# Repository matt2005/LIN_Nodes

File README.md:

Firmware and PCB designs for various LIN network nodes intended for retrofitting older vehicles.

```
boards/
    Eagle schematic and PCB files.

common/
    Protocol definitions and generator.

dashboard/
    Dashboard display using a 64x32 RGB LED panel driven by an NXP LPC1114.

Documentation/
    Datasheets for various parts used in the design.

lintool
    Host-side configuration tool. Talks to the usb_link hardware.

nodes/
    All of the nodes in this part of the tree are based on the Atmel ATTiny167.

    bl_core/
        LIN bootloader core, consumed by bl_installer.

    bl_installer/
        Bootloader installer; flashed onto a fresh board this will install the
        bootloader.

        The installed bootloader comes up on NAD 32 and can be flashed with lintool
        by explicitly supplying the node address and firmware file.

        lintool update -n 32 <path-to-fw-file>

        Only one node can be in this 'recovery' mode on the network when doing this.

    lib/
        Shared code.

    master/
        Network master node. Supports 7 switch-to-battery and 14 switch-to-ground
        inputs. 4 of the switch-to-ground inputs can also be 0-5V voltage inputs,
        with optional 2 or 16mA current sources for measuring resistive sensors.

    power_v3/
        5-output power switching node using Freescale smart high-side switches.
        Board limited to 5.5A, but code should work with the 10A device as well.
        Outputs support PWM, current monitoring, open- and short-circuit detection,
        overcurrent and overtemperature protection, etc.

    usb_link/
        USB bridge with support for configuration and node firmware updates.

```

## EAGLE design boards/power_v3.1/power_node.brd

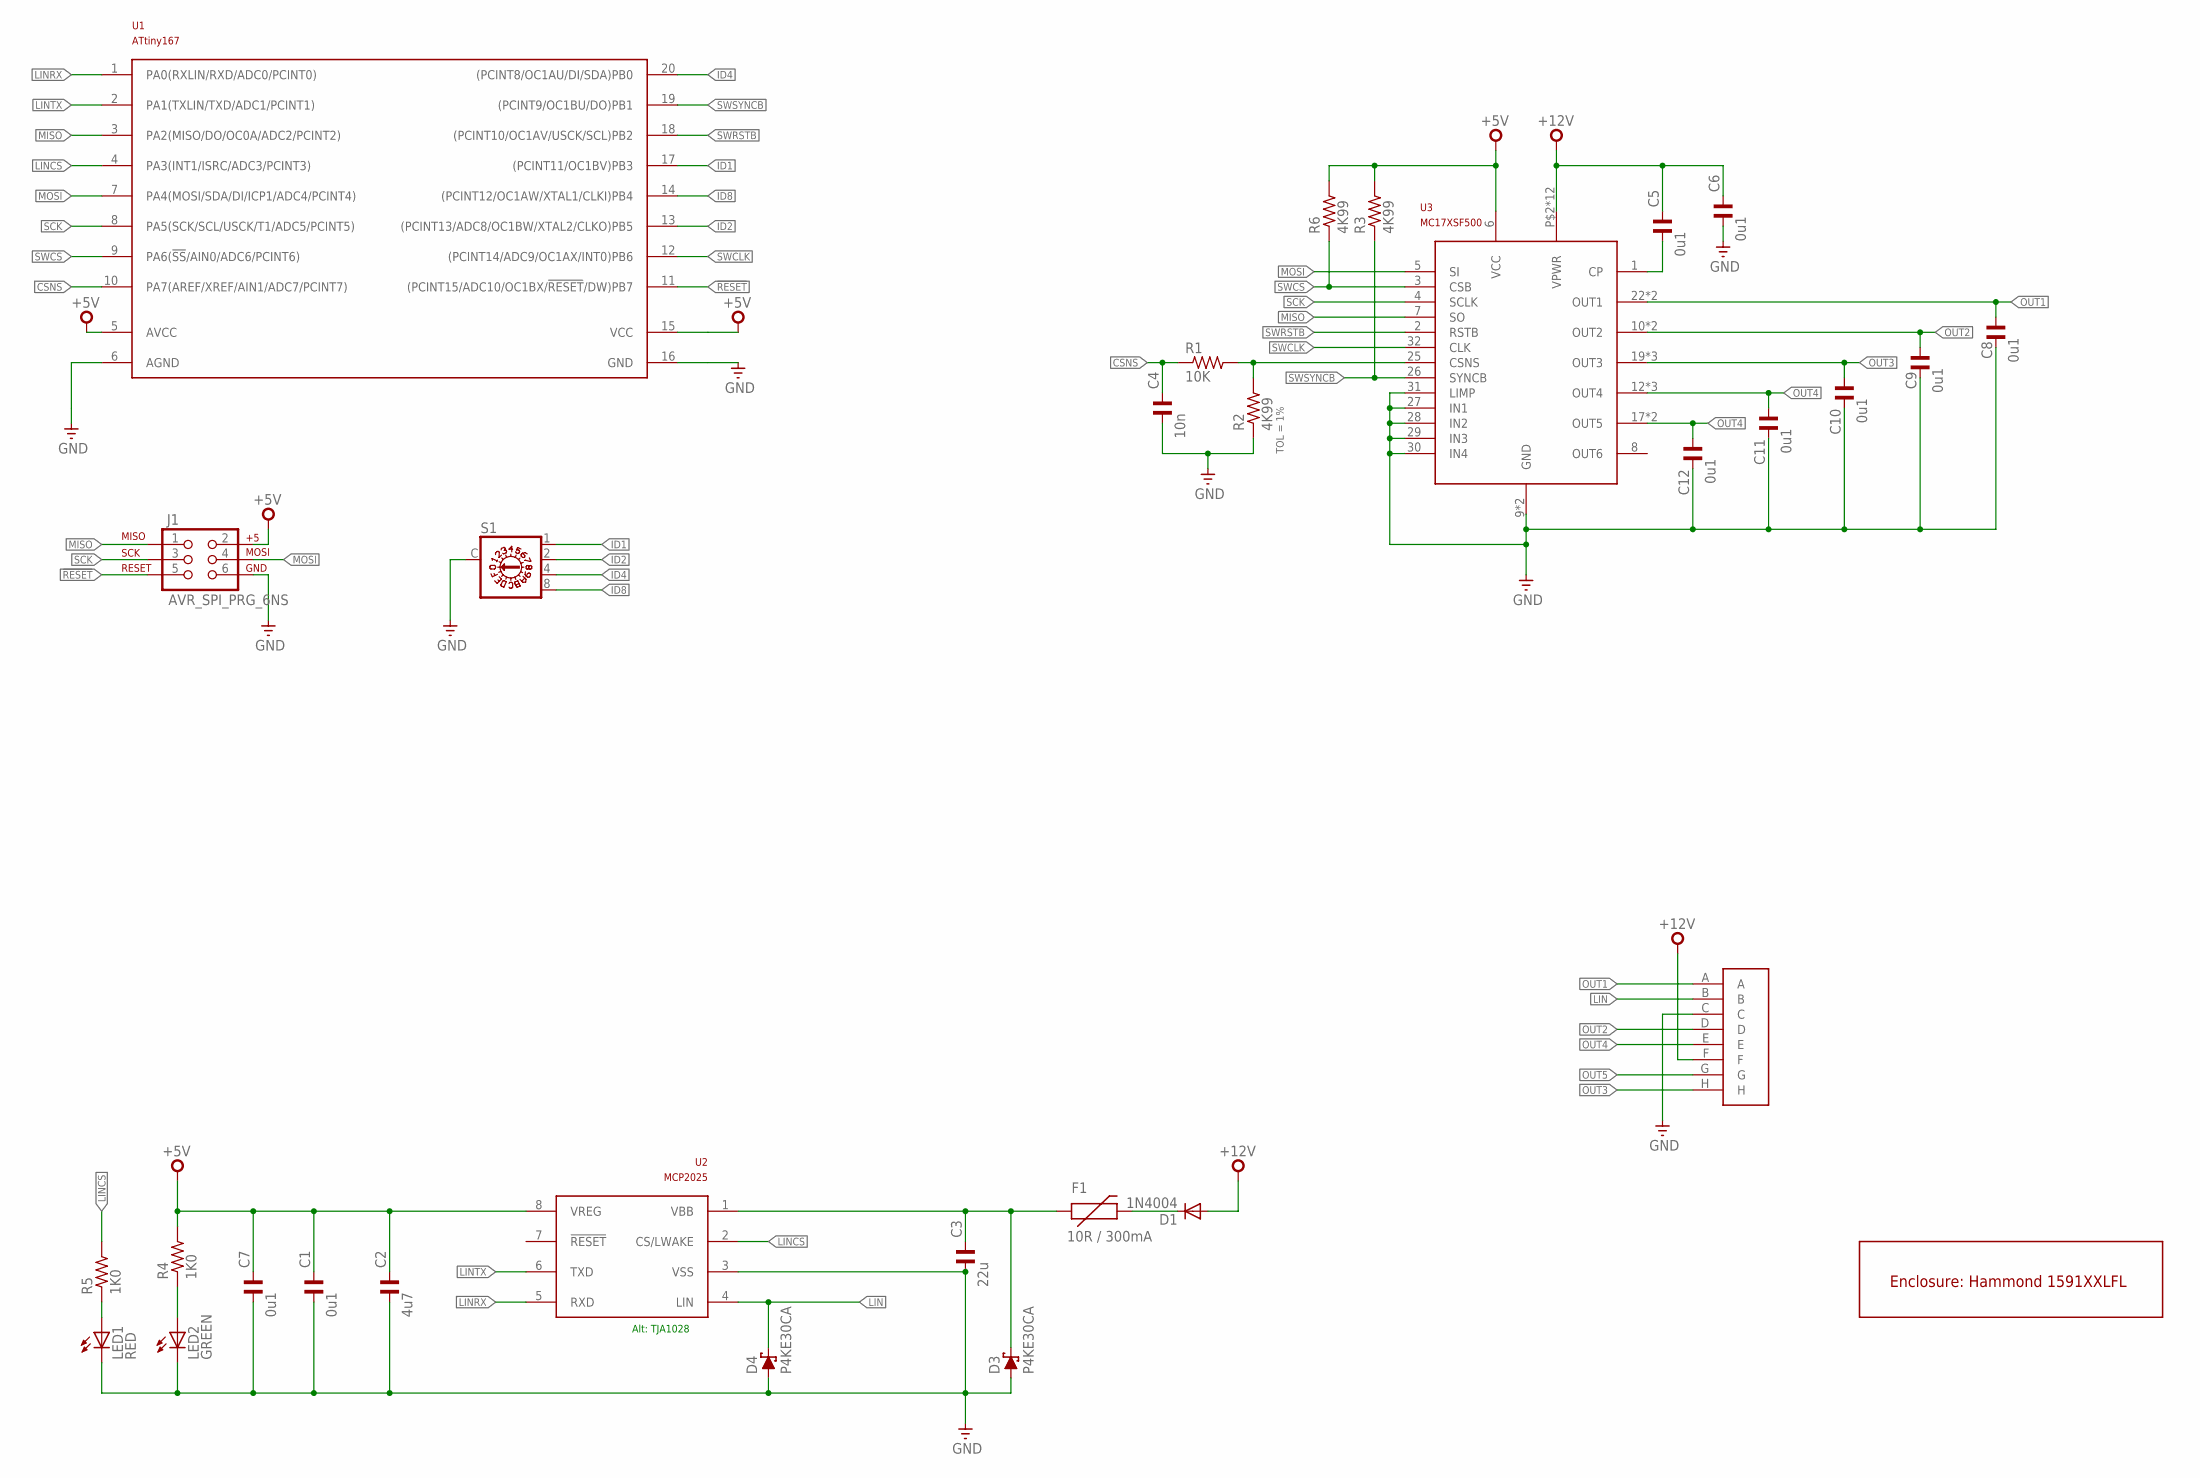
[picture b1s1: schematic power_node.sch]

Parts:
C1, C5, C6, C7: 0u1; C050-024X044; PARTNO FK28X7R1H104K
C2: 4u7; C050-024X044; PARTNO FK28X5R0J475K
C3: 22u; C050-024X044; PARTNO FK22X5R1E226M
C4: 10n; C025-024X044; PARTNO FK18X7R1H103K
C8, C9, C10, C11, C12: 0u1; C0603K; PARTNO C1608X7R1H104M080AA
D1: 1N4004; DO41-10; PARTNO 1N4004-TP
D3, D4: P4KE30CA; DO41-10; PARTNO P4KE30CA
F1: 10R / 300mA; PTC; PARTNO CMF-RL10-0
J1: AVR_SPI_PRG_6NS; 2X3-NS
J2: 12146734; PARTNO 12146724-B
LED1: RED; LED3MM; PARTNO C4SMF-RJS-CT0W0BB2
LED2: GREEN; LED3MM; PARTNO C4SMF-GJS-CV0Y0792
R1: 10K; 0207/10; PARTNO CF14JT10K0
R2, R3, R6: 4K99; 0207/10; PARTNO MFR-25FBF52-4K99
R4, R5: 1K0; 0207/10; PARTNO CF14JT1K00
S1: P103; PARTNO SH-7050MC
U1: ATtiny167; SO20W; PARTNO ATTINY167-SU
U2: MCP2025; SO08; PARTNO MCP2025-500E/SN
U3: MC17XSF500; SOIC32W-EP; PARTNO MC17XSF500EK
U$1: 1591XXLFL; PARTNO 1591XXLFLBK

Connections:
!RESET: J1.5, U1.11 ((PCINT15/ADC10/OC1BX/!RESET!/DW)PB7)
+5V: C1.1, C2.1, C7.1, J1.2, R3.2, R4.2, R6.2, U1.5 (AVCC), U1.15 (VCC), U2.8 (VREG), U3.6 (VCC)
+12V: C5.1, C6.1, D1.A, J2.F, U3.P$2 (VPWR), U3.P$3 (VPWR), U3.P$4 (VPWR), U3.P$5 (VPWR), U3.P$6 (VPWR), U3.P$7 (VPWR), U3.P$8 (VPWR), U3.P$9 (VPWR), U3.P$10 (VPWR), U3.P$11 (VPWR), U3.P$12 (VPWR), U3.P$13 (VPWR)
CSNS: C4.1, R1.1, U1.10 (PA7(AREF/XREF/AIN1/ADC7/PCINT7))
GND: C1.2, C2.2, C3.2, C4.2, C6.2, C7.2, C8.2, C9.2, C10.2, C11.2, C12.2, D3.A, D4.A, J1.6, J2.C, LED1.K (C), LED2.K (C), R2.1, S1.C, U1.6 (AGND), U1.16 (GND), U2.3 (VSS), U3.9 (GND), U3.24 (GND), U3.27 (IN1), U3.28 (IN2), U3.29 (IN3), U3.30 (IN4), U3.31 (LIMP)
ID1: S1.1, U1.17 ((PCINT11/OC1BV)PB3)
ID2: S1.2, U1.13 ((PCINT13/ADC8/OC1BW/XTAL2/CLKO)PB5)
ID4: S1.4, U1.20 ((PCINT8/OC1AU/DI/SDA)PB0)
ID8: S1.8, U1.14 ((PCINT12/OC1AW/XTAL1/CLKI)PB4)
LIN: D4.C, J2.B, U2.4 (LIN)
LINCS: R5.2, U1.4 (PA3(INT1/ISRC/ADC3/PCINT3)), U2.2 (CS/LWAKE)
LINRX: U1.1 (PA0(RXLIN/RXD/ADC0/PCINT0)), U2.5 (RXD)
LINTX: U1.2 (PA1(TXLIN/TXD/ADC1/PCINT1)), U2.6 (TXD)
MISO: J1.1, U1.3 (PA2(MISO/DO/OC0A/ADC2/PCINT2)), U3.7 (SO)
MOSI: J1.4, U1.7 (PA4(MOSI/SDA/DI/ICP1/ADC4/PCINT4)), U3.5 (SI)
unnamed: C5.2, U3.1 (CP)
unnamed: C3.1, D3.C, F1.P$1 (1), U2.1 (VBB)
unnamed: LED1.A, R5.1
unnamed: LED2.A, R4.1
unnamed: D1.C, F1.P$2 (2)
unnamed: R1.2, R2.2, U3.25 (CSNS)
OUT1: C8.1, J2.A, U3.22 (OUT1), U3.23 (OUT1)
OUT2: C9.1, J2.D, U3.10 (OUT2), U3.11 (OUT2)
OUT3: C10.1, J2.H, U3.19 (OUT3), U3.20 (OUT3), U3.21 (OUT3)
OUT4: C11.1, J2.E, U3.12 (OUT4), U3.13 (OUT4), U3.14 (OUT4)
OUT5: C12.1, J2.G, U3.17 (OUT5), U3.18 (OUT5)
SCK: J1.3, U1.8 (PA5(SCK/SCL/USCK/T1/ADC5/PCINT5)), U3.4 (SCLK)
SWCLK: U1.12 ((PCINT14/ADC9/OC1AX/INT0)PB6), U3.32 (CLK)
SWCS: R6.1, U1.9 (PA6(!SS!/AIN0/ADC6/PCINT6)), U3.3 (CSB)
SWRSTB: U1.18 ((PCINT10/OC1AV/USCK/SCL)PB2), U3.2 (RSTB)
SWSYNCB: R3.1, U1.19 ((PCINT9/OC1BU/DO)PB1), U3.26 (SYNCB)

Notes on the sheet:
Alt: TJA1028

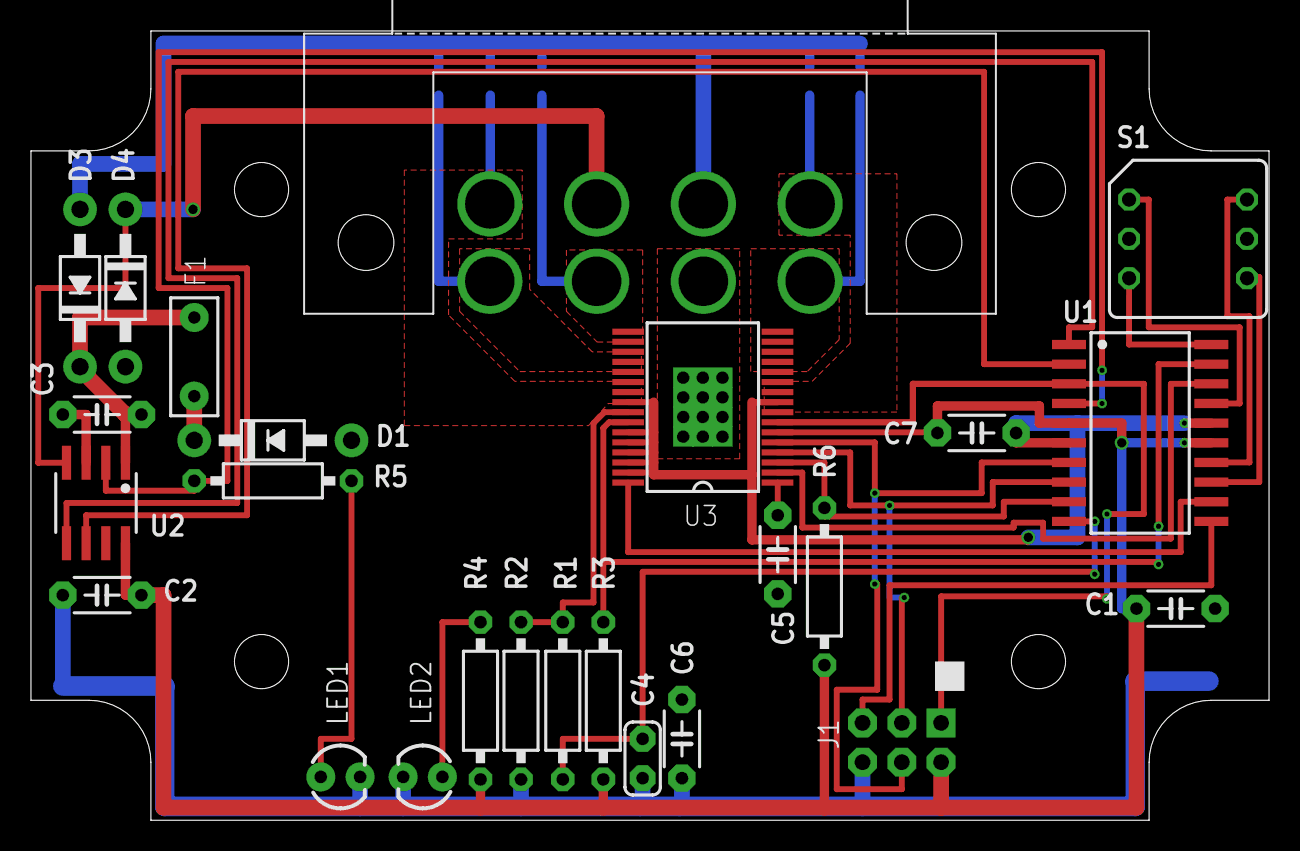
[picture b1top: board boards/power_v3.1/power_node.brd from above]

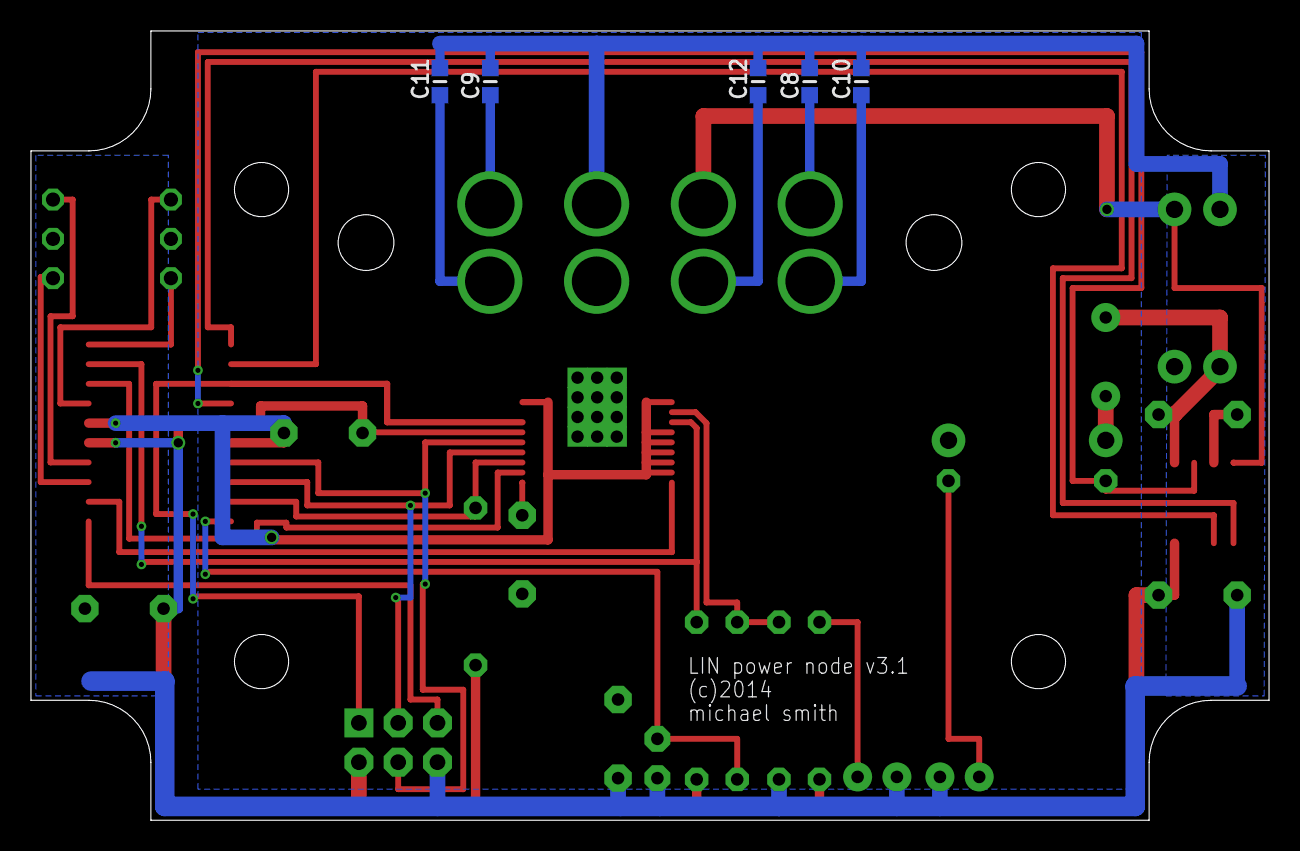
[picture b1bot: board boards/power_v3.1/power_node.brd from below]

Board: 2 copper layers, 80.0 x 51.0 mm, 31 parts (5 on the bottom side), 31 nets.

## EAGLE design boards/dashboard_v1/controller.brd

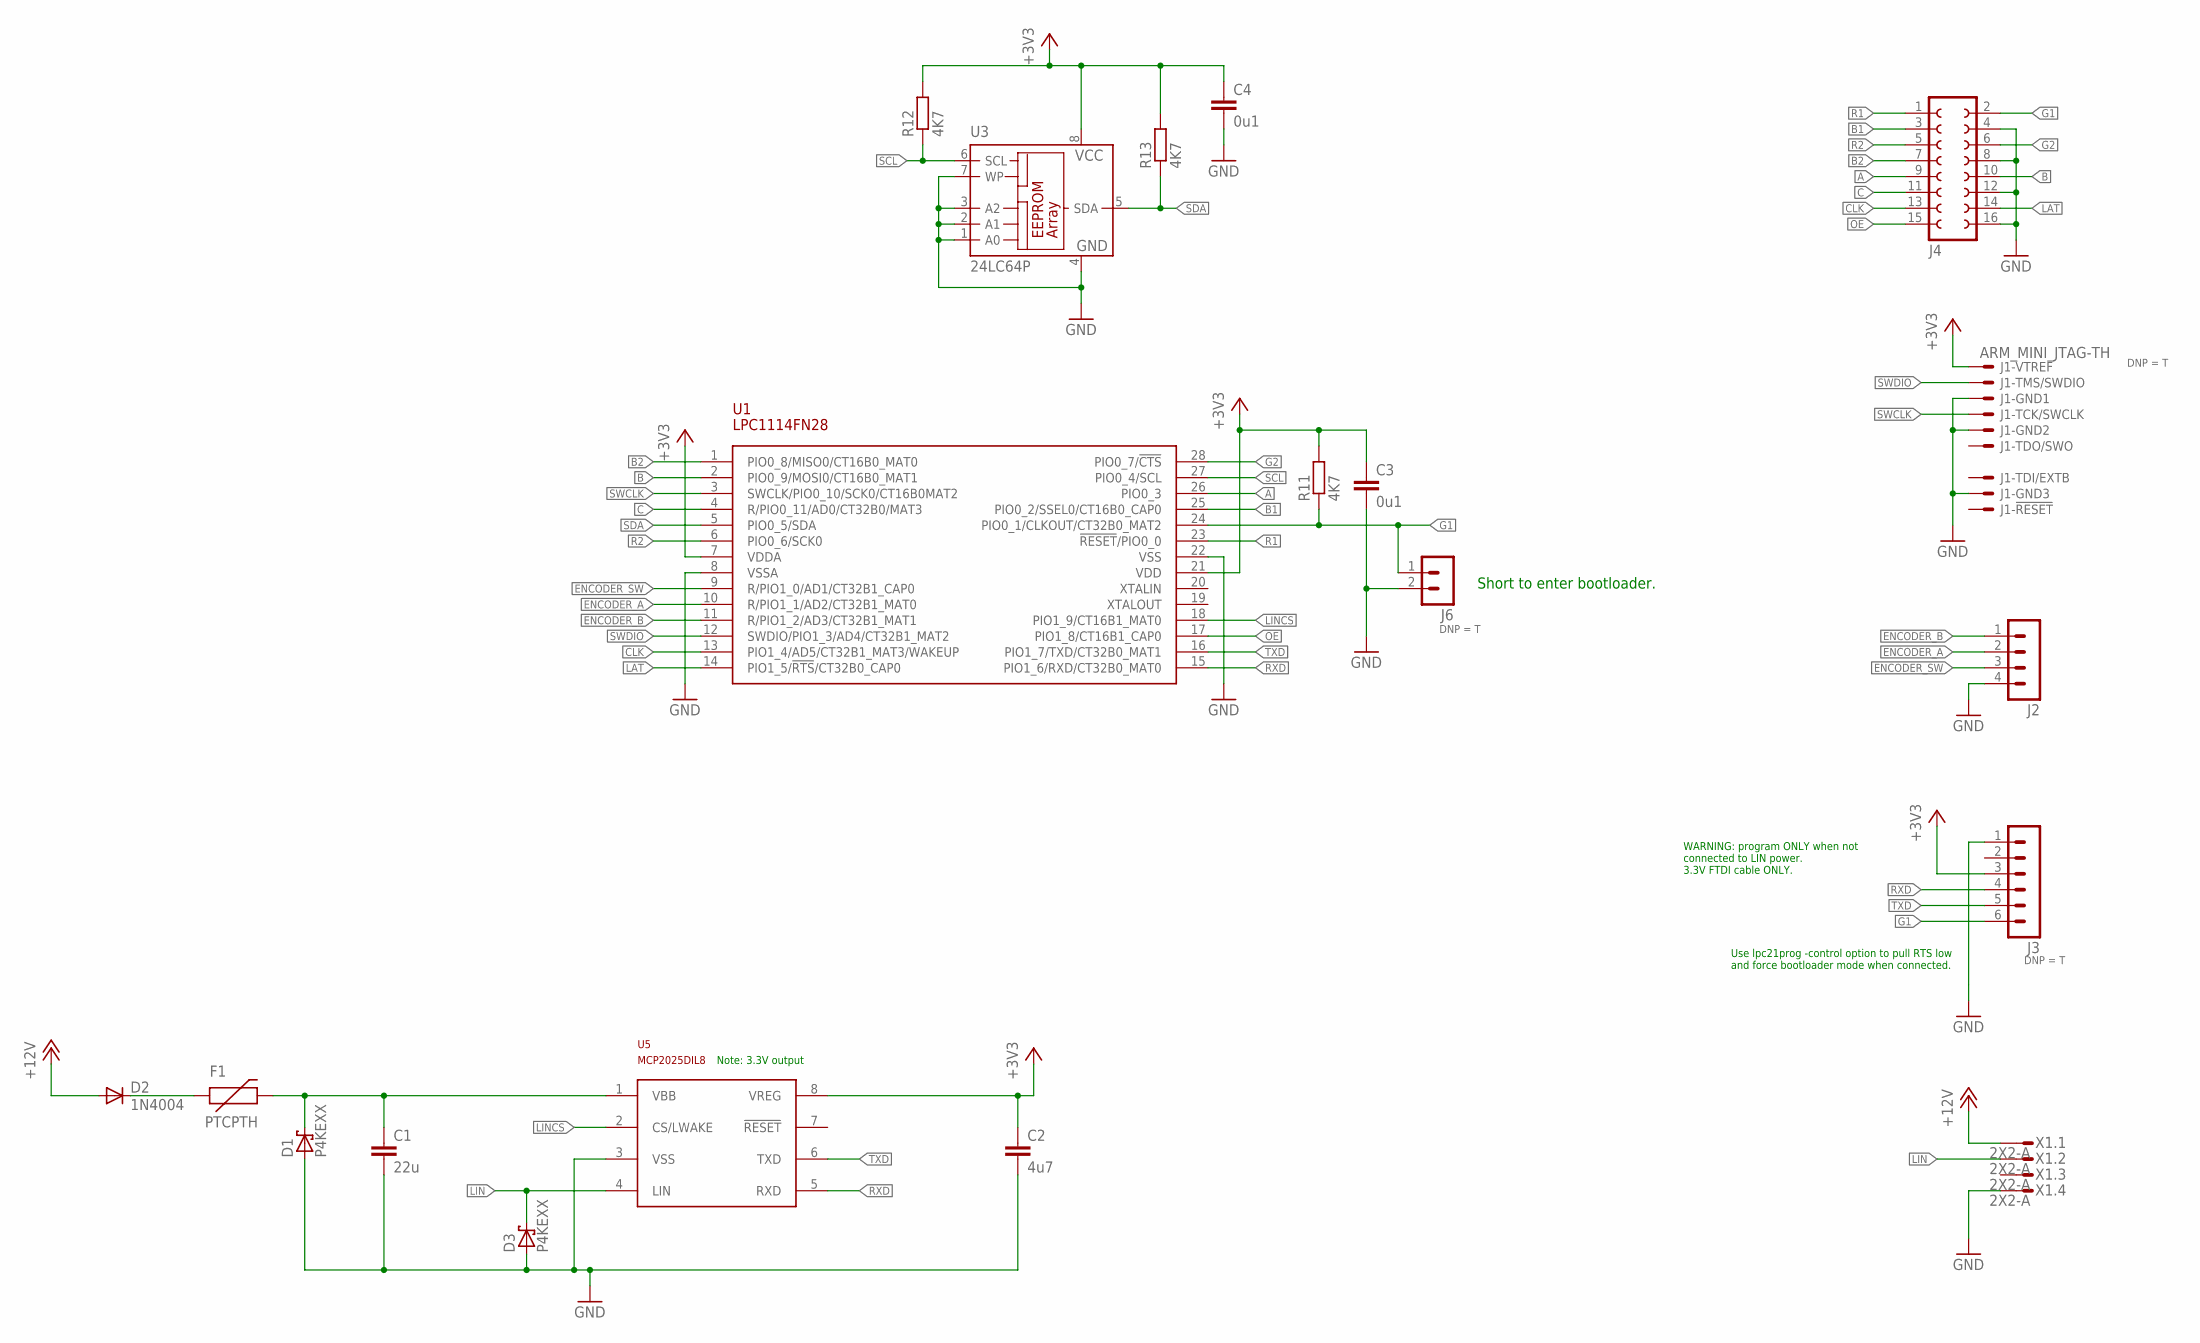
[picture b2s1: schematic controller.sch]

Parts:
C1: 22u; C050-024X044; PARTNO FK22X5R1E226M
C2: 4u7; C050-024X044; PARTNO FK28X5R0J475K
C3, C4: 0u1; C050-024X044; PARTNO FK28X7R1H104K
D1, D3: P4KEXX; DO41-10; PARTNO P4KE30CA
D2: 1N4004; DO41-10; PARTNO 1N4004-TP
F1: PTCPTH; PTC; PARTNO CMF-RL10-0
J1: ARM_MINI_JTAG-TH; FTSH-105-01-XXX-DV; PARTNO *
J2: MA04-1; PARTNO 640454-4
J3: MA06-1; PARTNO *
J4: FE08-2; PARTNO PPTC082LFBN-RC
J6: MA02-1Y
R11, R12, R13: 4K7; 0207/10; PARTNO MFR-25FBF52-4K99
U1: LPC1114FN28; DIL28; PARTNO LPC1114FN28/102,12
U3: 24LC64P; DIL8; PARTNO 24LC64-I/P
U5: MCP2025DIL8; DIL8; PARTNO MCP2025-330E/P
X1: 2X2-A; 3-794618-4; PARTNO 3-794618-4

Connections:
+3V3: C2.1, C3.1, C4.1, J1.1, J3.3, R11.2, R12.2, R13.2, U1.7 (VDDA), U1.21 (VDD), U3.8 (VCC), U5.8 (VREG)
+12V: D2.A, X1.1
A: J4.9, U1.26 (PIO0_3)
B: J4.10, U1.2 (PIO0_9/MOSI0/CT16B0_MAT1)
B1: J4.3, U1.25 (PIO0_2/SSEL0/CT16B0_CAP0)
B2: J4.7, U1.1 (PIO0_8/MISO0/CT16B0_MAT0)
C: J4.11, U1.4 (R/PIO0_11/AD0/CT32B0/MAT3)
CLK: J4.13, U1.13 (PIO1_4/AD5/CT32B1_MAT3/WAKEUP)
ENCODER_A: J2.2, U1.10 (R/PIO1_1/AD2/CT32B1_MAT0)
ENCODER_B: J2.1, U1.11 (R/PIO1_2/AD3/CT32B1_MAT1)
ENCODER_SW: J2.3, U1.9 (R/PIO1_0/AD1/CT32B1_CAP0)
G1: J3.6, J4.2, J6.1, R11.1, U1.24 (PIO0_1/CLKOUT/CT32B0_MAT2)
G2: J4.6, U1.28 (PIO0_7/!CTS)
GND: C1.2, C2.2, C3.2, C4.2, D1.A, D3.A, J1.3, J1.5, J1.9, J2.4, J3.1, J4.4, J4.8, J4.12, J4.16, J6.2, U1.8 (VSSA), U1.22 (VSS), U3.1 (A0), U3.2 (A1), U3.3 (A2), U3.4 (GND), U3.7 (WP), U5.3 (VSS), X1.4
LAT: J4.14, U1.14 (PIO1_5/!RTS!/CT32B0_CAP0)
LIN: D3.C, U5.4 (LIN), X1.2
LINCS: U1.18 (PIO1_9/CT16B1_MAT0), U5.2 (CS/LWAKE)
unnamed: C1.1, D1.C, F1.P$2 (2), U5.1 (VBB)
unnamed: D2.C, F1.P$1 (1)
OE: J4.15, U1.17 (PIO1_8/CT16B1_CAP0)
R1: J4.1, U1.23 (!RESET!/PIO0_0)
R2: J4.5, U1.6 (PIO0_6/SCK0)
RXD: J3.4, U1.15 (PIO1_6/RXD/CT32B0_MAT0), U5.5 (RXD)
SCL: R12.1, U1.27 (PIO0_4/SCL), U3.6 (SCL)
SDA: R13.1, U1.5 (PIO0_5/SDA), U3.5 (SDA)
SWCLK: J1.4, U1.3 (SWCLK/PIO0_10/SCK0/CT16B0MAT2)
SWDIO: J1.2, U1.12 (SWDIO/PIO1_3/AD4/CT32B1_MAT2)
TXD: J3.5, U1.16 (PIO1_7/TXD/CT32B0_MAT1), U5.6 (TXD)

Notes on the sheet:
Short to enter bootloader.
Use lpc21prog -control option to pull RTS low and force bootloader mode when connected.
Note: 3.3V output
WARNING: program ONLY when not connected to LIN power. 3.3V FTDI cable ONLY.

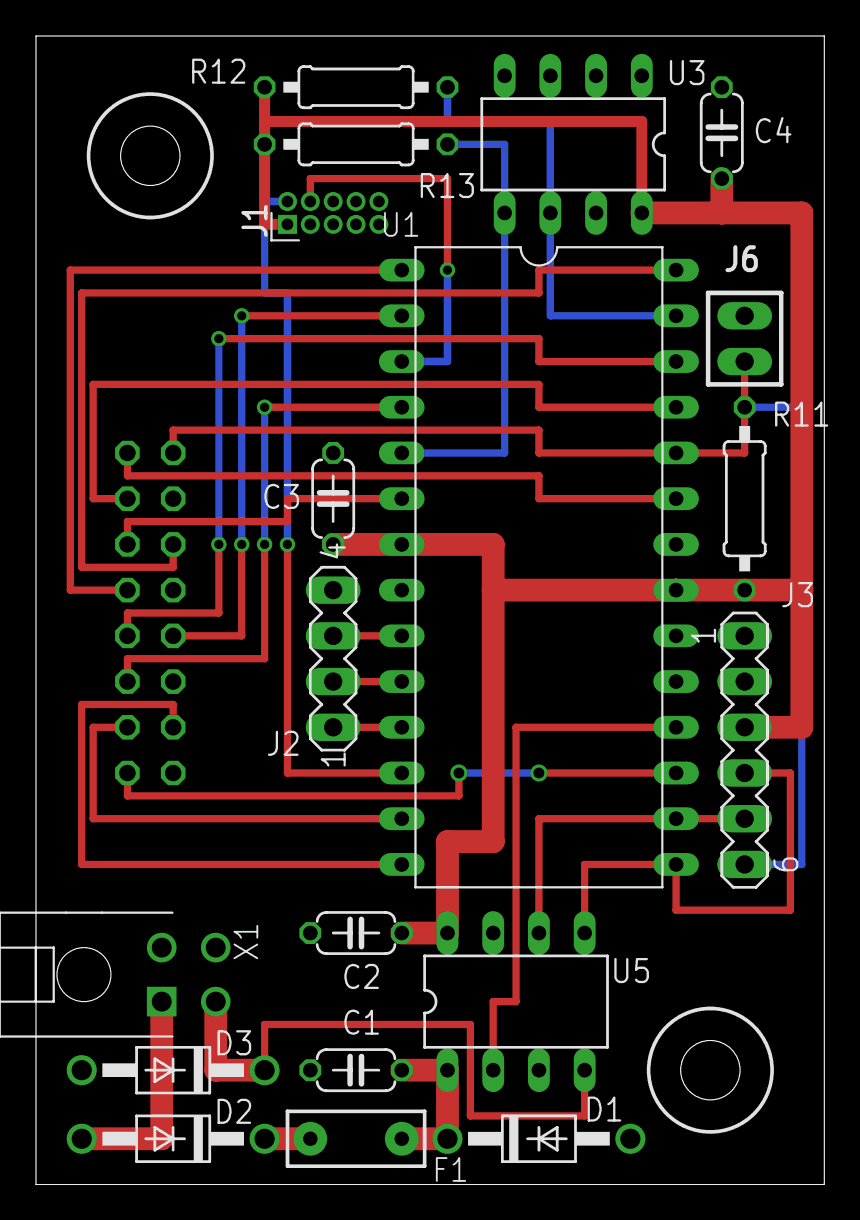
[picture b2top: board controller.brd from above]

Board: 2 copper layers, 43.8 x 63.8 mm, 22 parts (1 on the bottom side), 28 nets.

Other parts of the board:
U$1, U$2: 3,3

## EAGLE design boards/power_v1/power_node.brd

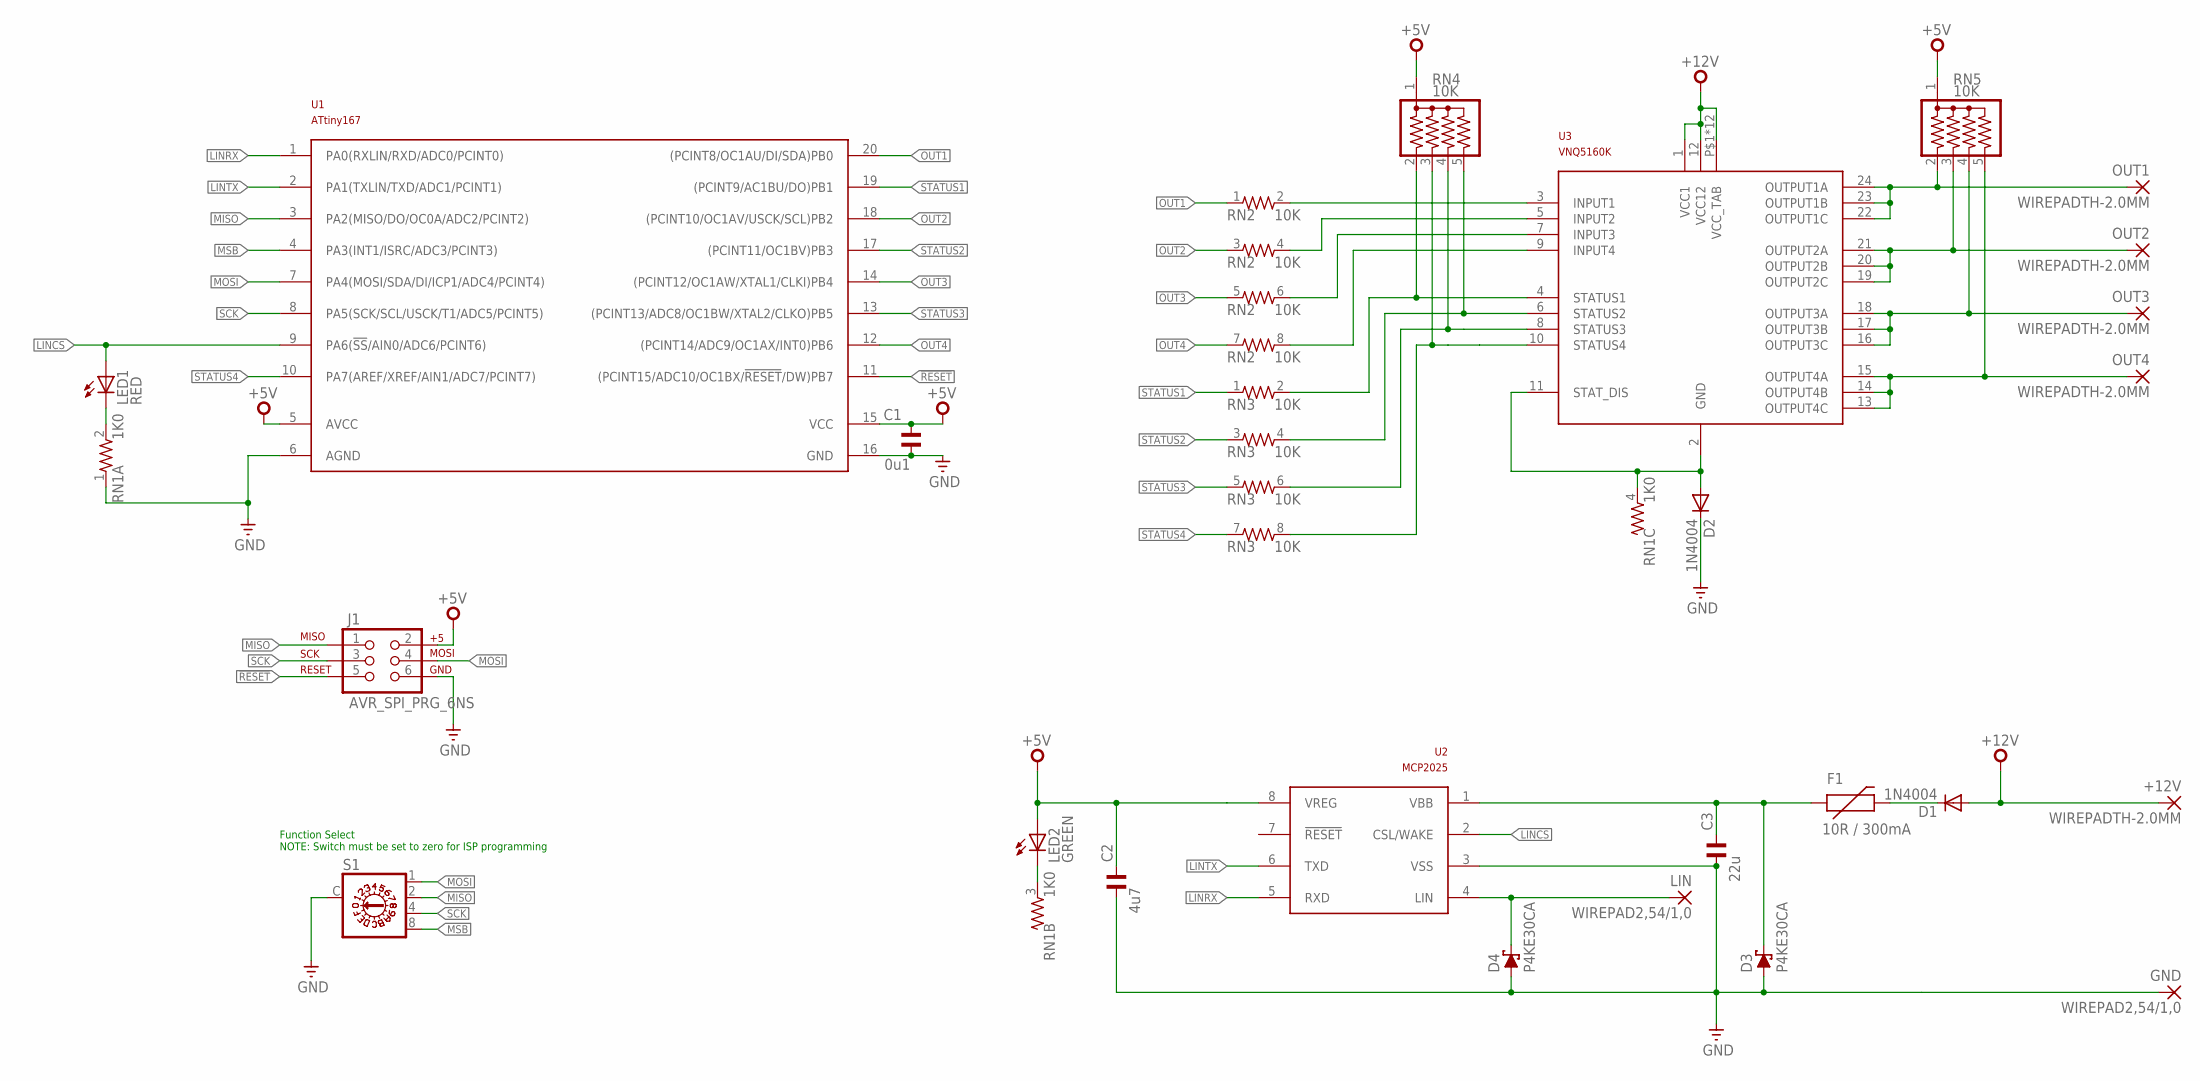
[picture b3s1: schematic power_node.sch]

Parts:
+12V: WIREPADTH-2.0MM; WIREPAD-TH-2.0MM
C1: 0u1; C025-024X044; PARTNO FK28X7R1H104K
C2: 4u7; C050-024X044; PARTNO FK28X5R0J475K
C3: 22u; C050-024X044; PARTNO FK22X5R1E226M
D1, D2: 1N4004; DO41-10; PARTNO 1N4004-TP
D3, D4: P4KE30CA; DO41-10; PARTNO P4KE30CA
F1: 10R / 300mA; PTC; PARTNO 600R150-RBZR
GND: WIREPAD2,54/1,0; 2,54/1,0
J1: AVR_SPI_PRG_6NS; 2X3-NS
LED1: RED; LED3MM; PARTNO C4SMF-RJS-CT0W0BB2
LED2: GREEN; LED3MM; PARTNO C4SMF-GJS-CV0Y0792
LIN: WIREPAD2,54/1,0; 2,54/1,0
OUT1, OUT2, OUT3, OUT4: WIREPADTH-2.0MM; WIREPAD-TH-2.0MM
RN1: 1K0; SIL4; PARTNO 4604X-101-103LF
RN2, RN3: 10K; SIL8; PARTNO 4608X-102-103LF
RN4, RN5: 10K; SIL5; PARTNO 4605X-101-103LF
S1: P103; PARTNO SH-7050MC
U1: ATtiny167; SO20W; PARTNO ATTINY167-SU
U2: MCP2025; SO08; PARTNO MCP2025-500E/SN
U3: VNQ5160K; POWERSSO24; PARTNO VNQ5E160KTR-E

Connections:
!RESET: J1.5, U1.11 ((PCINT15/ADC10/OC1BX/!RESET!/DW)PB7)
+5V: C1.1, C2.1, J1.2, LED2.A, RN4.1, RN5.1, U1.5 (AVCC), U1.15 (VCC), U2.8 (VREG)
+12V: +12V.1, D1.A, U3.1 (VCC1), U3.12 (VCC12), U3.P$1 (VCC_TAB), U3.P$2 (VCC_TAB), U3.P$3 (VCC_TAB), U3.P$4 (VCC_TAB), U3.P$5 (VCC_TAB), U3.P$6 (VCC_TAB), U3.P$7 (VCC_TAB), U3.P$8 (VCC_TAB), U3.P$9 (VCC_TAB), U3.P$10 (VCC_TAB), U3.P$11 (VCC_TAB), U3.P$12 (VCC_TAB)
GND: C1.2, C2.2, C3.2, D2.C, D3.A, D4.A, GND.1, J1.6, RN1.1, S1.C, U1.6 (AGND), U1.16 (GND), U2.3 (VSS)
LINCS: LED1.A, U1.9 (PA6(!SS!/AIN0/ADC6/PCINT6)), U2.2 (CSL/WAKE)
LINRX: U1.1 (PA0(RXLIN/RXD/ADC0/PCINT0)), U2.5 (RXD)
LINTX: U1.2 (PA1(TXLIN/TXD/ADC1/PCINT1)), U2.6 (TXD)
MISO: J1.1, S1.2, U1.3 (PA2(MISO/DO/OC0A/ADC2/PCINT2))
MOSI: J1.4, S1.1, U1.7 (PA4(MOSI/SDA/DI/ICP1/ADC4/PCINT4))
MSB: S1.8, U1.4 (PA3(INT1/ISRC/ADC3/PCINT3))
unnamed: D4.C, LIN.1, U2.4 (LIN)
unnamed: C3.1, D3.C, F1.P$1 (1), U2.1 (VBB)
unnamed: LED1.K (C), RN1.2
unnamed: LED2.K (C), RN1.3 (2)
unnamed: D1.C, F1.P$2 (2)
unnamed: RN3.8 (2), RN4.3, U3.10 (STATUS4)
unnamed: RN3.6 (2), RN4.4, U3.8 (STATUS3)
unnamed: D2.A, RN1.4 (2), U3.2 (GND), U3.11 (STAT_DIS)
unnamed: RN3.4 (2), RN4.5, U3.6 (STATUS2)
unnamed: RN3.2, RN4.2, U3.4 (STATUS1)
unnamed: RN2.2, U3.3 (INPUT1)
unnamed: RN2.8 (2), U3.9 (INPUT4)
unnamed: RN2.6 (2), U3.7 (INPUT3)
unnamed: RN2.4 (2), U3.5 (INPUT2)
OUT1: RN2.1, U1.20 ((PCINT8/OC1AU/DI/SDA)PB0)
OUT2: RN2.3 (1), U1.18 ((PCINT10/OC1AV/USCK/SCL)PB2)
OUT3: RN2.5 (1), U1.14 ((PCINT12/OC1AW/XTAL1/CLKI)PB4)
OUT4: RN2.7 (1), U1.12 ((PCINT14/ADC9/OC1AX/INT0)PB6)
OUTPUT1: OUT1.1, RN5.2, U3.22 (OUTPUT1C), U3.23 (OUTPUT1B), U3.24 (OUTPUT1A)
OUTPUT2: OUT2.1, RN5.3, U3.19 (OUTPUT2C), U3.20 (OUTPUT2B), U3.21 (OUTPUT2A)
OUTPUT3: OUT3.1, RN5.4, U3.16 (OUTPUT3C), U3.17 (OUTPUT3B), U3.18 (OUTPUT3A)
OUTPUT4: OUT4.1, RN5.5, U3.13 (OUTPUT4C), U3.14 (OUTPUT4B), U3.15 (OUTPUT4A)
SCK: J1.3, S1.4, U1.8 (PA5(SCK/SCL/USCK/T1/ADC5/PCINT5))
STATUS1: RN3.1, U1.19 ((PCINT9/AC1BU/DO)PB1)
STATUS2: RN3.3 (1), U1.17 ((PCINT11/OC1BV)PB3)
STATUS3: RN3.5 (1), U1.13 ((PCINT13/ADC8/OC1BW/XTAL2/CLKO)PB5)
STATUS4: RN3.7 (1), U1.10 (PA7(AREF/XREF/AIN1/ADC7/PCINT7))

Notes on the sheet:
Function Select NOTE: Switch must be set to zero for ISP programming

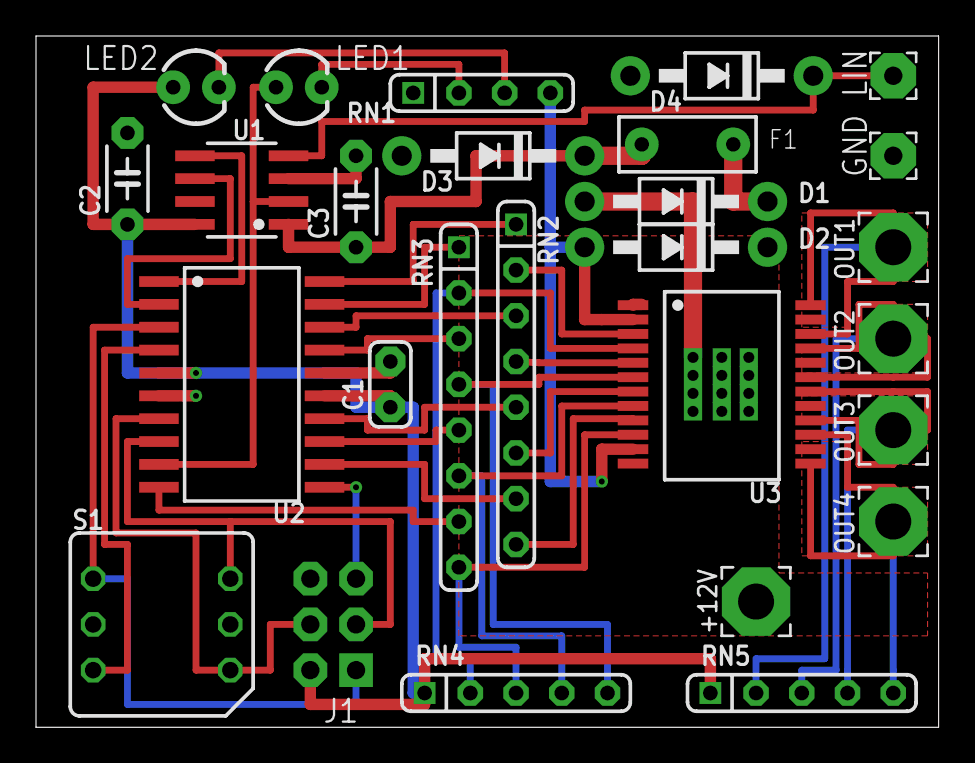
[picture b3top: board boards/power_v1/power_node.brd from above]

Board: 2 copper layers, 50.1 x 38.4 mm, 27 parts (0 on the bottom side), 37 nets.

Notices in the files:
nodes/usb_link/micronucleus/configuration/t167_lin/bootloaderconfig.h:
License: GNU GPL v2 (see License.txt
boards/master_v1/lin_master_node.brd:
©2014 michael smith
